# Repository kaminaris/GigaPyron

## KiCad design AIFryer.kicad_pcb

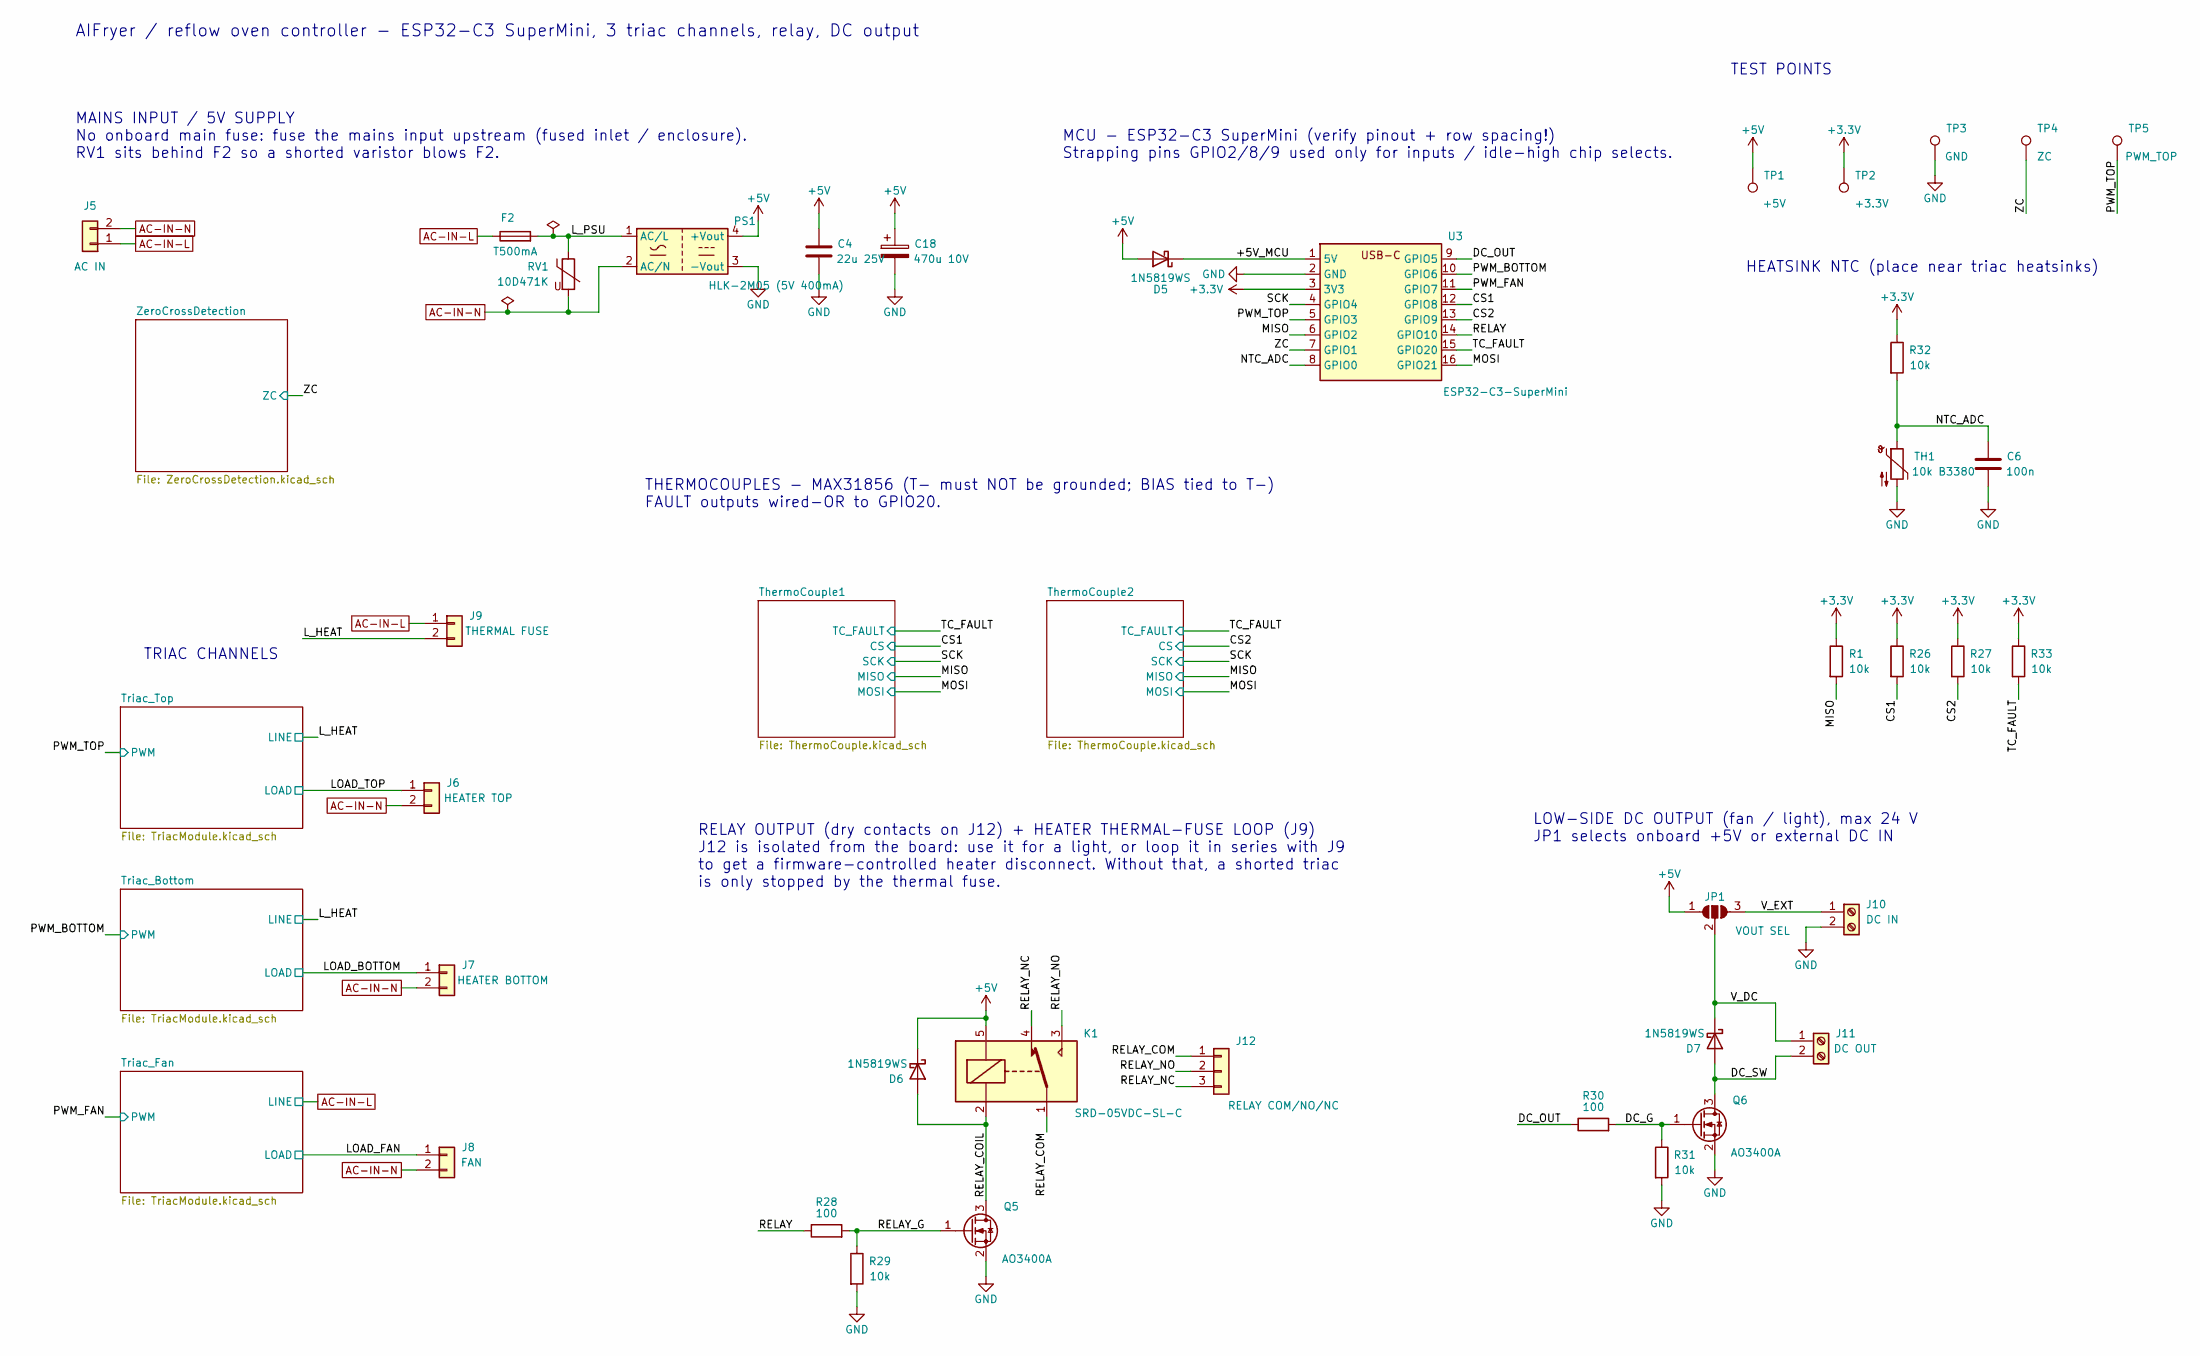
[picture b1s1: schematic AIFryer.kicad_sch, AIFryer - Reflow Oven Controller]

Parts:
C4: 22u 25V; C_1206_3216Metric; MPN C12891
C6: 100n; C_0603_1608Metric; MPN C14663
C18: 470u 10V; CP_Elec_6.3x7.7; MPN C55388431
D5, D6, D7: 1N5819WS; D_SOD-323; MPN C191023
F2: T500mA; Fuse_Littelfuse_372_D8.50mm; MPN C529783
J5: AC IN; TerminalBlock_Phoenix_PT-1,5-2-5.0-H_1x02_P5.00mm_Horizontal; MPN C5188434
J6: HEATER TOP; TerminalBlock_Phoenix_PT-1,5-2-5.0-H_1x02_P5.00mm_Horizontal; MPN C5188434
J7: HEATER BOTTOM; TerminalBlock_Phoenix_PT-1,5-2-5.0-H_1x02_P5.00mm_Horizontal; MPN C5188434
J8: FAN; TerminalBlock_Phoenix_PT-1,5-2-5.0-H_1x02_P5.00mm_Horizontal; MPN C5188434
J9: THERMAL FUSE; TerminalBlock_Phoenix_PT-1,5-2-5.0-H_1x02_P5.00mm_Horizontal; MPN C5188434
J10: DC IN; TerminalBlock_Phoenix_PT-1,5-2-3.5-H_1x02_P3.50mm_Horizontal; MPN C695629
J11: DC OUT; TerminalBlock_Phoenix_PT-1,5-2-3.5-H_1x02_P3.50mm_Horizontal; MPN C695629
J12: RELAY COM/NO/NC; TerminalBlock_Phoenix_PT-1,5-3-5.0-H_1x03_P5.00mm_Horizontal; MPN C5188435
JP1: VOUT SEL; SolderJumper-3_P1.3mm_Open_RoundedPad1.0x1.5mm
K1: SRD-05VDC-SL-C; Relay_SPDT_SANYOU_SRD_Series_Form_C; MPN C35449
PS1: HLK-2M05 (5V 400mA); Converter_ACDC_Hi-Link_HLK-2Mxx; MPN C209909
Q5, Q6: AO3400A; SOT-23; MPN C20917
R1, R26, R27, R29, R31, R32, R33: 10k; R_0603_1608Metric; MPN C25804
R28, R30: 100; R_0603_1608Metric; MPN C22775
RV1: 10D471K; RV_Disc_D12mm_W4.2mm_P7.5mm; MPN C8760
TH1: 10k B3380; R_0603_1608Metric; MPN C13564
TP1: +5V; TestPoint_THTPad_D1.5mm_Drill0.7mm
TP2: +3.3V; TestPoint_THTPad_D1.5mm_Drill0.7mm
TP3: GND; TestPoint_THTPad_D1.5mm_Drill0.7mm
TP4: ZC; TestPoint_THTPad_D1.5mm_Drill0.7mm
TP5: PWM_TOP; TestPoint_THTPad_D1.5mm_Drill0.7mm
U3: ESP32-C3-SuperMini

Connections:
+3.3V: R1.1, R26.1, R27.1, R32.1, R33.1, TP2.1 (1_1), U3.3 (3V3); also elsewhere on the board
+5V: C4.1, C18.1, D5.2 (A), D6.1 (K), JP1.1 (A), K1.5, PS1.4 (+Vout), TP1.1 (1_1)
/+5V_MCU: D5.1 (K), U3.1 (5V)
/CS1: R26.2, U3.12 (GPIO8); also elsewhere on the board
/CS2: R27.2, U3.13 (GPIO9); also elsewhere on the board
/DC_G: Q6.1 (G), R30.2, R31.1
/DC_OUT: R30.1, U3.9 (GPIO5)
/DC_SW: D7.2 (A), J11.2, Q6.3 (D)
/LOAD_BOTTOM: J7.1; also elsewhere on the board
/LOAD_FAN: J8.1; also elsewhere on the board
/LOAD_TOP: J6.1; also elsewhere on the board
/L_HEAT: J9.2; also elsewhere on the board
/L_PSU: F2.2, PS1.1 (AC/L), RV1.1
/MISO: R1.2, U3.6 (GPIO2); also elsewhere on the board
/MOSI: U3.16 (GPIO21); also elsewhere on the board
/NTC_ADC: C6.1, R32.2, TH1.1, U3.8 (GPIO0)
/PWM_BOTTOM: U3.10 (GPIO6); also elsewhere on the board
/PWM_FAN: U3.11 (GPIO7); also elsewhere on the board
/PWM_TOP: TP5.1 (1_1), U3.5 (GPIO3); also elsewhere on the board
/RELAY: R28.1, U3.14 (GPIO10)
/RELAY_COIL: D6.2 (A), K1.2, Q5.3 (D)
/RELAY_COM: J12.1, K1.1
/RELAY_G: Q5.1 (G), R28.2, R29.1
/RELAY_NC: J12.3, K1.4
/RELAY_NO: J12.2, K1.3
/SCK: U3.4 (GPIO4); also elsewhere on the board
/TC_FAULT: R33.2, U3.15 (GPIO20); also elsewhere on the board
/V_DC: D7.1 (K), J11.1, JP1.2 (C)
/V_EXT: J10.1, JP1.3 (B)
/ZC: TP4.1 (1_1), U3.7 (GPIO1); also elsewhere on the board
AC-IN-L: F2.1, J5.1, J9.1; also elsewhere on the board
AC-IN-N: J5.2, J6.2, J7.2, J8.2, PS1.2 (AC/N), RV1.2; also elsewhere on the board
GND: C4.2, C6.2, C18.2, J10.2, PS1.3 (-Vout), Q5.2 (S), Q6.2 (S), R29.2, R31.2, TH1.2, TP3.1 (1_1), U3.2 (GND); also elsewhere on the board

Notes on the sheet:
TRIAC CHANNELS
THERMOCOUPLES - MAX31856 (T- must NOT be grounded; BIAS tied to T-) FAULT outputs wired-OR to GPIO20.
MAINS INPUT / 5V SUPPLY No onboard main fuse: fuse the mains input upstream (fused inlet / enclosure). RV1 sits behind F2 so a shorted varistor blows F2.
HEATSINK NTC (place near triac heatsinks)
MCU - ESP32-C3 SuperMini (verify pinout + row spacing!) Strapping pins GPIO2/8/9 used only for inputs / idle-high chip selects.
AIFryer / reflow oven controller - ESP32-C3 SuperMini, 3 triac channels, relay, DC output
RELAY OUTPUT (dry contacts on J12) + HEATER THERMAL-FUSE LOOP (J9) J12 is isolated from the board: use it for a light, or loop it in series with J9 to get a firmware-controlled heater disconnect. Without that, a shorted triac is only stopped by the thermal fuse.
TEST POINTS
LOW-SIDE DC OUTPUT (fan / light), max 24 V JP1 selects onboard +5V or external DC IN

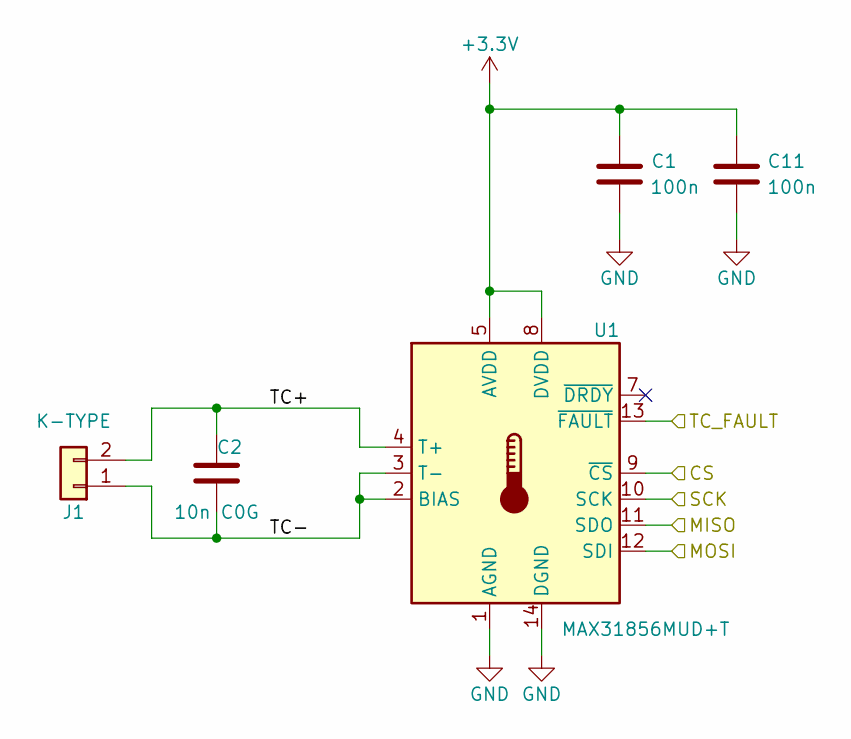
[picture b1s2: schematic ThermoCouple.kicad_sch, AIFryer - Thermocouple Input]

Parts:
C1, C11: 100n; C_0603_1608Metric; MPN C14663
C2: 10n C0G; C_0603_1608Metric; MPN C22399611
J1: K-TYPE; PhoenixContact_GMSTBA_2,5_2-G-7,62_1x02_P7.62mm_Horizontal; MPN C395930
U1: MAX31856MUD+T; TSSOP-14_4.4x5mm_P0.65mm; MPN C2653162

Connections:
+3.3V: C1.1, C11.1, U1.5 (AVDD), U1.8 (DVDD); also elsewhere on the board
/CS1: U1.9 (~CS); also elsewhere on the board
/MISO: U1.11 (SDO); also elsewhere on the board
/MOSI: U1.12 (SDI); also elsewhere on the board
/SCK: U1.10 (SCK); also elsewhere on the board
/TC_FAULT: U1.13 (~FAULT); also elsewhere on the board
/ThermoCouple1/TC+: C2.1, J1.2, U1.4 (T+)
/ThermoCouple1/TC-: C2.2, J1.1, U1.2 (BIAS), U1.3 (T-)
GND: C1.2, C11.2, U1.1 (AGND), U1.14 (DGND); also elsewhere on the board

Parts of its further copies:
C3: 10n C0G; C_0603_1608Metric; MPN C22399611
C5, C12: 100n; C_0603_1608Metric; MPN C14663
J2: K-TYPE; PhoenixContact_GMSTBA_2,5_2-G-7,62_1x02_P7.62mm_Horizontal; MPN C395930
U2: MAX31856MUD+T; TSSOP-14_4.4x5mm_P0.65mm; MPN C2653162

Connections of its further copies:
+3.3V: C5.1, C12.1, U2.5 (AVDD), U2.8 (DVDD); also elsewhere on the board
/CS2: U2.9 (~CS); also elsewhere on the board
/MISO: U2.11 (SDO); also elsewhere on the board
/MOSI: U2.12 (SDI); also elsewhere on the board
/SCK: U2.10 (SCK); also elsewhere on the board
/TC_FAULT: U2.13 (~FAULT); also elsewhere on the board
/ThermoCouple2/TC+: C3.1, J2.2, U2.4 (T+)
/ThermoCouple2/TC-: C3.2, J2.1, U2.2 (BIAS), U2.3 (T-)
GND: C5.2, C12.2, U2.1 (AGND), U2.14 (DGND); also elsewhere on the board

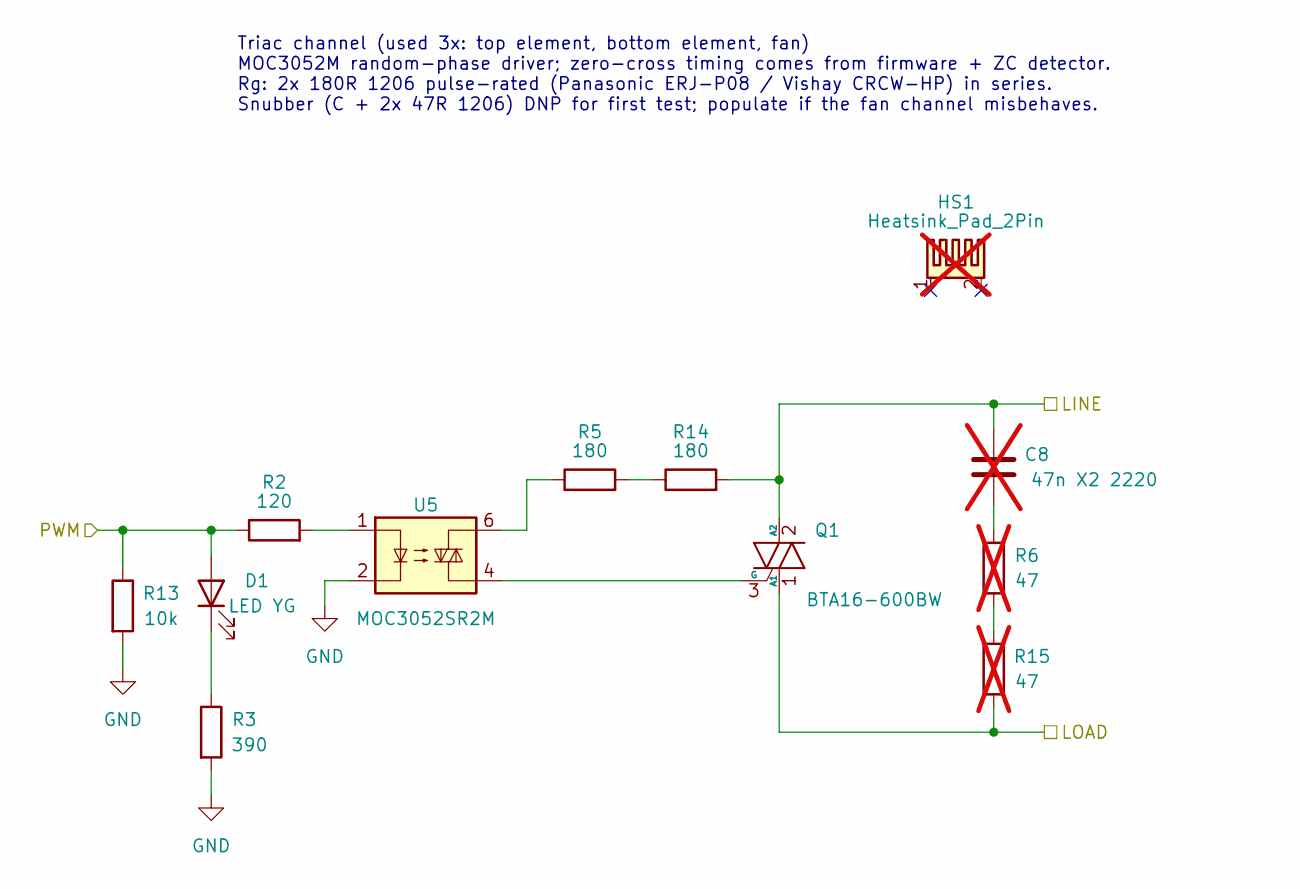
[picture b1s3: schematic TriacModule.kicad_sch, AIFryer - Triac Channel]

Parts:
C8: 47n X2 2220; C_2220_5750Metric; MPN C5331998; not fitted
D1: LED YG; LED_0603_1608Metric; MPN C2987554
HS1: Heatsink_Pad_2Pin; Heatsink36x11; not fitted
Q1: BTA16-600BW; TO-220-3_Horizontal_TabUp; MPN C87396
R2: 120; R_0603_1608Metric; MPN C22787
R3: 390; R_0603_1608Metric; MPN C23151
R5, R14: 180; R_1206_3216Metric; MPN C20166761
R6, R15: 47; R_1206_3216Metric; not fitted
R13: 10k; R_0603_1608Metric; MPN C25804
U5: MOC3052SR2M; SMDIP-6_W9.53mm; MPN C19864

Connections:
/LOAD_TOP: Q1.1 (A1), R15.2; also elsewhere on the board
/L_HEAT: C8.1, Q1.2 (A2), R14.2; also elsewhere on the board
/PWM_TOP: D1.2 (A), R2.1, R13.1; also elsewhere on the board
GND: R3.2, R13.2, U5.2; also elsewhere on the board
unnamed: C8.2, R6.1
unnamed: D1.1 (K), R3.1
unnamed: Q1.3 (G), U5.4
unnamed: R2.2, U5.1
unnamed: R5.1, U5.6
unnamed: R5.2, R14.1
unnamed: R6.2, R15.1

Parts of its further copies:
C9, C10: 47n X2 2220; C_2220_5750Metric; MPN C5331998; not fitted
D3, D4: LED YG; LED_0603_1608Metric; MPN C2987554
Q2, Q4: BTA16-600BW; TO-220-3_Horizontal_TabUp; MPN C87396
R4, R20: 390; R_0603_1608Metric; MPN C23151
R8, R21: 120; R_0603_1608Metric; MPN C22787
R11, R17, R22, R23: 180; R_1206_3216Metric; MPN C20166761
R12, R18, R24, R25: 47; R_1206_3216Metric; not fitted
R16, R19: 10k; R_0603_1608Metric; MPN C25804
U7, U8: MOC3052SR2M; SMDIP-6_W9.53mm; MPN C19864

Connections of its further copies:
/LOAD_BOTTOM: Q2.1 (A1), R18.2; also elsewhere on the board
/LOAD_FAN: Q4.1 (A1), R25.2; also elsewhere on the board
/L_HEAT: C9.1, Q2.2 (A2), R17.2; also elsewhere on the board
/PWM_BOTTOM: D3.2 (A), R8.1, R16.1; also elsewhere on the board
/PWM_FAN: D4.2 (A), R19.1, R21.1; also elsewhere on the board
AC-IN-L: C10.1, Q4.2 (A2), R23.2; also elsewhere on the board
GND: R4.2, R16.2, R19.2, R20.2, U7.2, U8.2; also elsewhere on the board
unnamed: C9.2, R12.1
unnamed: C10.2, R24.1
unnamed: D3.1 (K), R4.1
unnamed: D4.1 (K), R20.1
unnamed: Q2.3 (G), U7.4
unnamed: Q4.3 (G), U8.4
unnamed: R8.2, U7.1
unnamed: R11.1, U7.6
unnamed: R11.2, R17.1
unnamed: R12.2, R18.1
unnamed: R21.2, U8.1
unnamed: R22.1, U8.6
unnamed: R22.2, R23.1
unnamed: R24.2, R25.1

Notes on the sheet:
Triac channel (used 3x: top element, bottom element, fan) MOC3052M random-phase driver; zero-cross timing comes from firmware + ZC detector. Rg: 2x 180R 1206 pulse-rated (Panasonic ERJ-P08 / Vishay CRCW-HP) in series. Snubber (C + 2x 47R 1206) DNP for first test; populate if the fan channel misbeha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

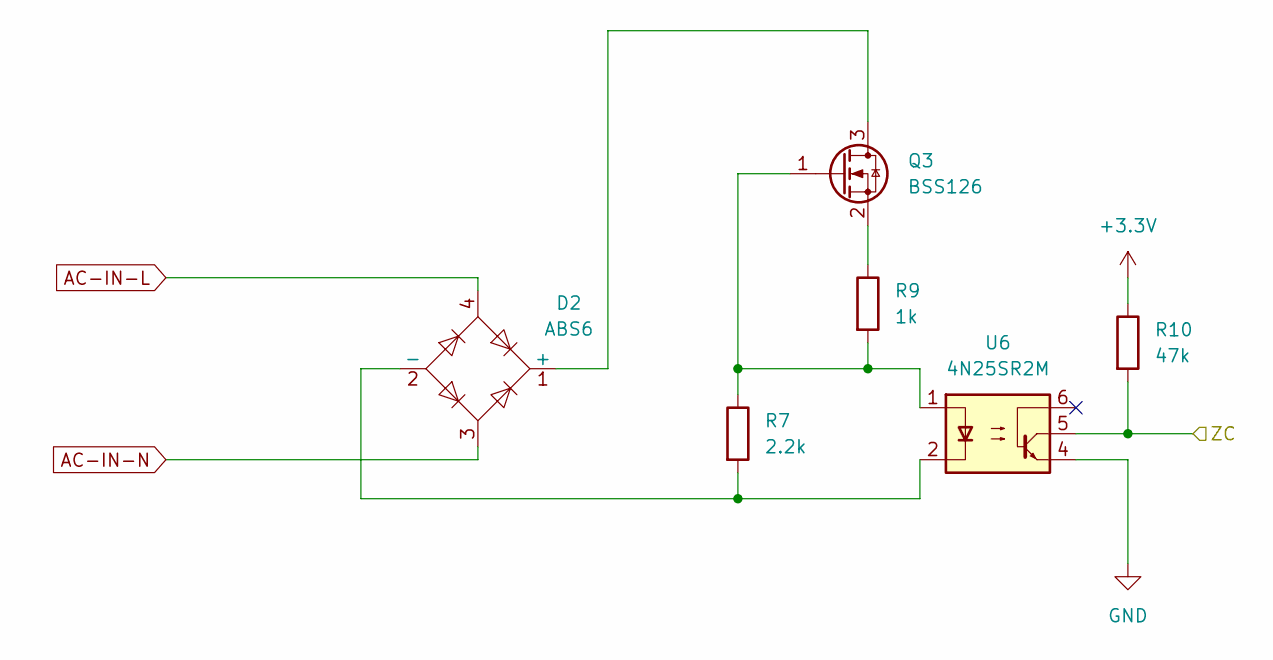
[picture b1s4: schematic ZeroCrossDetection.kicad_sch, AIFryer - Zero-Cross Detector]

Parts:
D2: ABS6; Diode_Bridge_Diotec_ABS; MPN C54444726
Q3: BSS126; SOT-23; MPN C2987085; JLCRotOffset 0
R7: 2.2k; R_0603_1608Metric; MPN C4190
R9: 1k; R_0603_1608Metric; MPN C21190
R10: 47k; R_0603_1608Metric; MPN C25819
U6: 4N25SR2M; SMDIP-6_W9.53mm; MPN C44165

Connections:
+3.3V: R10.1; also elsewhere on the board
/ZC: R10.2, U6.5; also elsewhere on the board
AC-IN-L: D2.4; also elsewhere on the board
AC-IN-N: D2.3; also elsewhere on the board
GND: U6.4; also elsewhere on the board
unnamed: D2.1 (+), Q3.3 (D)
unnamed: D2.2 (-), R7.2, U6.2
unnamed: Q3.1 (G), R7.1, R9.2, U6.1
unnamed: Q3.2 (S), R9.1

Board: 2 copper layers, 86 parts (19 on the bottom side), 62 nets, no tracks yet.

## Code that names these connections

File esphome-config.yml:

esphome:
    name: airfryergiga
    friendly_name: AirFryerGiga
    on_boot:
        priority: -10
        then:
            -   climate.control:
                    id: heater_pid
                    mode: "OFF"

esp32:
    board: esp32-c3-devkitm-1
    framework:
        type: arduino

# Enable logging
logger:
    level: INFO

web_server:
    port: 80

# Enable Home Assistant API
api:
    encryption:
        key: "QcAEDqWBE5+a54K05lTA758DqFT22hFX0pjWSj0PnSI="

ota:
    -   platform: esphome
        password: "e23d08bd1139cf9a569618494aa8ccc2"

wifi:
    ssid: !secret wifi_ssid
    password: !secret wifi_password

    # Enable fallback hotspot (captive portal) in case wifi connection fails
    ap:
        ssid: "Airfryergiga Fallback Hotspot"
        password: "rasejTdp0N1I"

captive_portal:

external_components:
    # equivalent shorthand for GitHub
    -   source: github://kaminaris/esphome-external-component-examples@d0ced0a3d11e5808571e7f6c730ffa50d71741f0
        components: [ passthru_float_output ]

number:
    -   platform: template
        name: "Duration (Minutes)"
        id: timer_duration
        min_value: 0
        max_value: 360  # Set the maximum to 6 hours (360 minutes)
        step: 10
        unit_of_measurement: "min"
        mode: slider  # Can be a slider for easy adjustments in Home Assistant
        optimistic: true  # Stores value even when not connected to the system

switch:
    -   platform: template
        id: fan_switch
        name: "Fan Switch"
        optimistic: True
        turn_on_action:
            then:
                -   lambda:
                        id(ac_fan).set_level(0.55);
        turn_off_action:
            then:
                -   lambda:
                        id(ac_fan).set_level(0);
                        id(ac_fan).turn_off();
globals:
    - id: start_time
      type: unsigned long
      restore_value: false

script:
    # Script to handle the timer logic
    -   id: heater_fan_timer_script
        mode: single
        then:
            -   climate.control:
                    id: heater_pid
                    mode: "HEAT"
            -   switch.turn_on: fan_switch
            -   logger.log:
                    format: "Heater and fan turned ON. Timer started."
                    level: INFO
            -   lambda: |-
                    id(start_time) = millis();
            -   delay: !lambda 'return id(timer_duration).state * 60 * 1000;'
            -   climate.control:
                    id: heater_pid
                    mode: "OFF"
            -   switch.turn_off: fan_switch
            -   lambda: |-
                    id(start_time) = 0;
            -   logger.log:
                    format: "Heater and fan turned OFF after timer expired."
                    level: INFO
interval:
    -   interval: 60s
        then:
            -   lambda: |-
                    if (id(start_time) > 0) {
                        unsigned long elapsed_time = millis() - id(start_time);
                        int remaining_time = (id(timer_duration).state * 60 * 1000 - elapsed_time) / 60000;  // Remaining time in minutes
                        id(time_remaining).publish_state(remaining_time);  // Update remaining time
                        ESP_LOGI("main", "Time remaining: %d minutes", remaining_time);
                    }

button:
    -   platform: template
        name: "Stop Timer"
        on_press:
            then:
                -   script.stop: heater_fan_timer_script
                -   climate.control:
                        id: heater_pid
                        mode: "OFF"
                -   switch.turn_off: fan_switch
                -   logger.log: "Timer manually stopped and devices turned OFF."

    -   platform: template
        name: "Start heating"
        on_press:
            then:
                -   script.execute: heater_fan_timer_script
                -   logger.log: "Timer manually stopped and devices turned OFF."
climate:
    -   platform: pid
        name: "Air Fryer"
        sensor: main_temp
        id: heater_pid
        default_target_temperature: 0°C
        visual:
            min_temperature: 10
            max_temperature: 180
        heat_output: heat_output_redirect
        #heat_output: ac_heater
        on_state:
            then:
                -   lambda: |-
                        auto pidO = id(heat_output_redirect).valx;
                        auto pidX = id(heater_pid).get_output_value();
                        float temp_diff = id(heater_pid).target_temperature - id(main_temp).state;
                        if (temp_diff > 20) {
                          //pidO = 1.0; 
                        } else if (temp_diff > 0) {
                          pidO = pidO * (temp_diff / 20.0); 
                        } else {
                          pidO = 0.0;
                        }
                        //ESP_LOGI("PID", "%.4f, %.4f, %.4f, %.4f", pidX, pidO, id(main_temp).state, temp_diff);
                        id(ac_heater).set_level(pidO);
        control_parameters:
            kp: 0.5
            ki: 0.0
            kd: 0.01
            output_averaging_samples: 1      # smooth the output over 5 samples
            derivative_averaging_samples: 1  # smooth the derivative value over 10 samples
        deadband_parameters:
            threshold_high: 0.1°C       # deadband within +/-0.5°C of target_temperature
            threshold_low: -0.1°C

spi:
    miso_pin: GPIO5
    clk_pin: GPIO19

sensor:
    -   platform: template
        name: "Time Remaining (Minutes)"
        id: time_remaining
        unit_of_measurement: "min"
        update_interval: 60s  # Update every 60 seconds

    -   platform: max6675
        id: main_temp
        name: "Temperature"
        cs_pin: GPIO2
        update_interval: 1s

output:
    -   platform: passthru_float_output
        id: heat_output_redirect

    -   platform: ac_dimmer
        id: ac_fan
        gate_pin: GPIO4
        method: LEADING
        zero_cross_pin:
            number: GPIO6
            allow_other_uses: true
            mode:
                input: true
            inverted: yes

    -   platform: ac_dimmer
        id: ac_heater
        gate_pin: GPIO3
        max_power: 0.5
        zero_cross_pin:
            number: GPIO6
            allow_other_uses: true
            mode:
                input: true
            inverted: yes
light:
    -   platform: monochromatic
        output: ac_heater
        name: Heater

    -   platform: monochromatic
        output: ac_fan
        name: Fan
